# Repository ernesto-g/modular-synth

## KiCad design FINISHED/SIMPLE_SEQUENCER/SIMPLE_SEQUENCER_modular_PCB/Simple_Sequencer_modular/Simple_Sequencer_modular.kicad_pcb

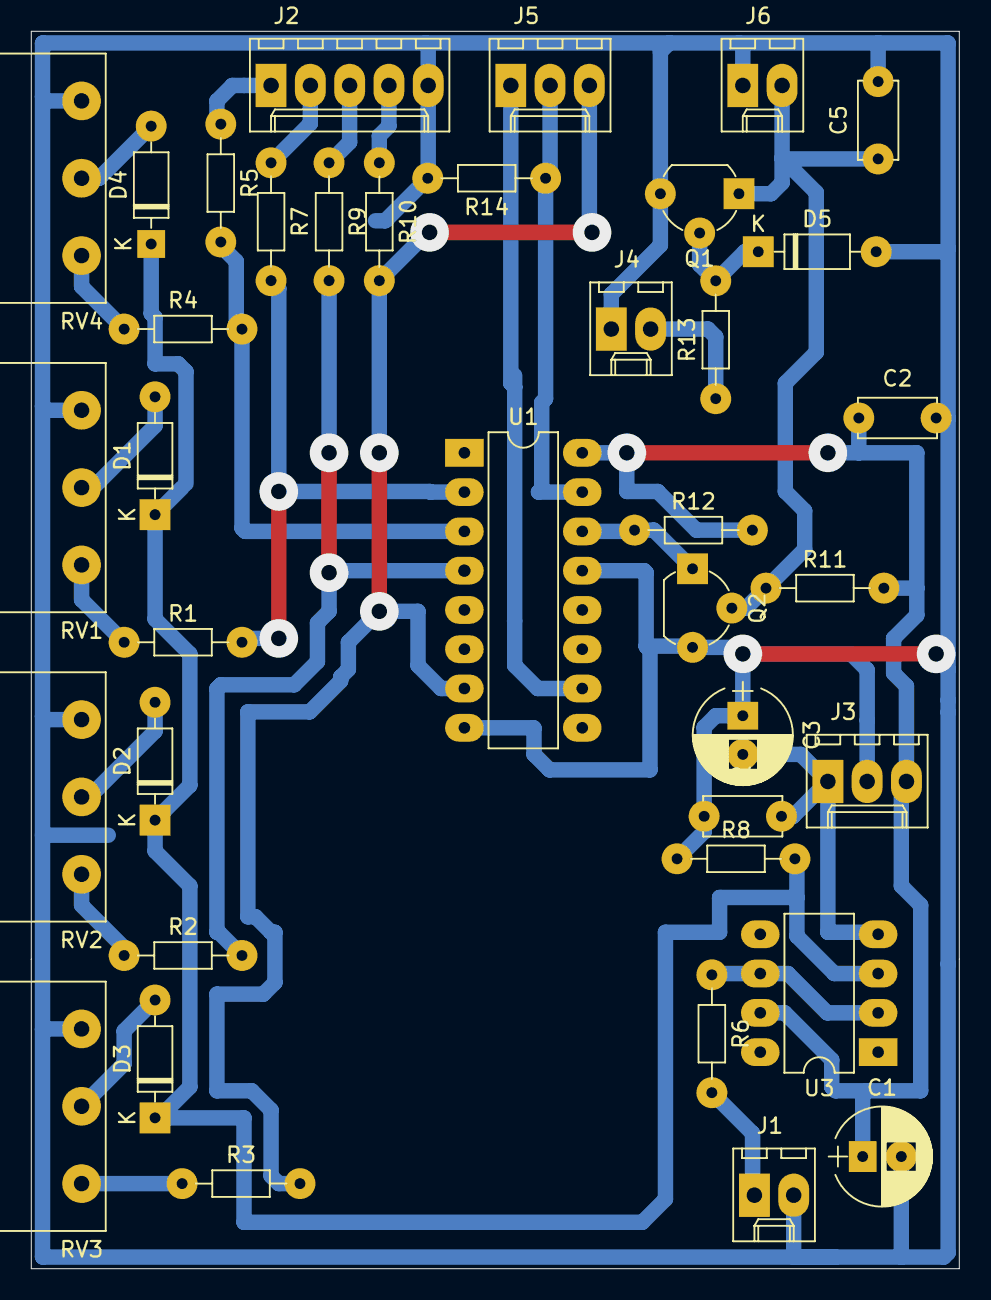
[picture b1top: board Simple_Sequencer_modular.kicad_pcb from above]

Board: 2 copper layers, 60.0 x 80.0 mm, 38 parts (0 on the bottom side), 28 nets.

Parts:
C1, C3: 100uFx25V; CP_Radial_D6.3mm_P2.50mm
C2, C4, C5: 100nF; C_Disc_D5.0mm_W2.5mm_P5.00mm
D1, D2, D3, D4, D5: 1N4148; D_DO-35_SOD27_P7.62mm_Horizontal
J1: CV_OUT; Molex_KK-6410-02_02x2.54mm_Straight
J2: LEDS_OUT; Molex_KK-6410-05_05x2.54mm_Straight
J3: POWER; Molex_KK-6410-03_03x2.54mm_Straight
J4: CLK_IN; Molex_KK-6410-02_02x2.54mm_Straight
J5: SW_STEPS; Molex_KK-6410-03_03x2.54mm_Straight
J6: BTN_STEP; Molex_KK-6410-02_02x2.54mm_Straight
Q1, Q2: BC547; TO-92_Wide
R1, R2, R3, R4: 10k; R_Axial_DIN0204_L3.6mm_D1.6mm_P7.62mm_Horizontal
R5, R7, R9, R10: 2.2k; R_Axial_DIN0204_L3.6mm_D1.6mm_P7.62mm_Horizontal
R6: 100; R_Axial_DIN0204_L3.6mm_D1.6mm_P7.62mm_Horizontal
R8, R11, R12, R13, R14: 100k; R_Axial_DIN0204_L3.6mm_D1.6mm_P7.62mm_Horizontal
RV1, RV2, RV3, RV4: 10K B; Potentiometer_Piher_PC-16_Single_Vertical
U1: 4017; DIP-16_W7.62mm_LongPads
U3: LM741; DIP-8_W7.62mm_LongPads

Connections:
+12V: C1.1, C2.1, J3.3, R11.2, R12.2, U1.16, U3.7
-12V: C3.2, C4.2, J3.1, U3.4
CLK: Q2.1, R12.1, U1.14
GND: C1.2, C2.2, C3.1, C4.1, C5.2, D5.2, J1.2, J2.5, J3.2, J4.1, J6.1, Q1.3, Q2.3, R8.1, R14.2, RV1.1, RV2.1, RV3.1, RV4.1, U1.8, U1.13
unnamed: C5.1, J6.2, Q1.1, Q2.2, R11.1
unnamed: D1.2, RV1.2
unnamed: D2.2, RV2.2
unnamed: D3.2, RV3.2
unnamed: D4.2, RV4.2
unnamed: D5.1, Q1.2, R13.2
unnamed: J1.1, R6.2
unnamed: J2.1, R5.1
unnamed: J2.2, R7.1
unnamed: J2.3, R9.1
unnamed: J2.4, R10.1
unnamed: J4.2, R13.1
unnamed: R1.1, RV1.3
unnamed: R2.1, RV2.3
unnamed: R3.1, RV3.3
unnamed: R4.1, RV4.3
unnamed: R6.1, U3.2, U3.6
Q0: R4.2, R5.2, U1.3
Q0_CV: D1.1, D2.1, D3.1, D4.1, R8.2, U3.3
Q1: R1.2, R7.2, U1.2
Q2: R2.2, R9.2, U1.4
Q3: J5.3, R3.2, R10.2, U1.7
Q4: J5.1, U1.10
RST: J5.2, R14.1, U1.15

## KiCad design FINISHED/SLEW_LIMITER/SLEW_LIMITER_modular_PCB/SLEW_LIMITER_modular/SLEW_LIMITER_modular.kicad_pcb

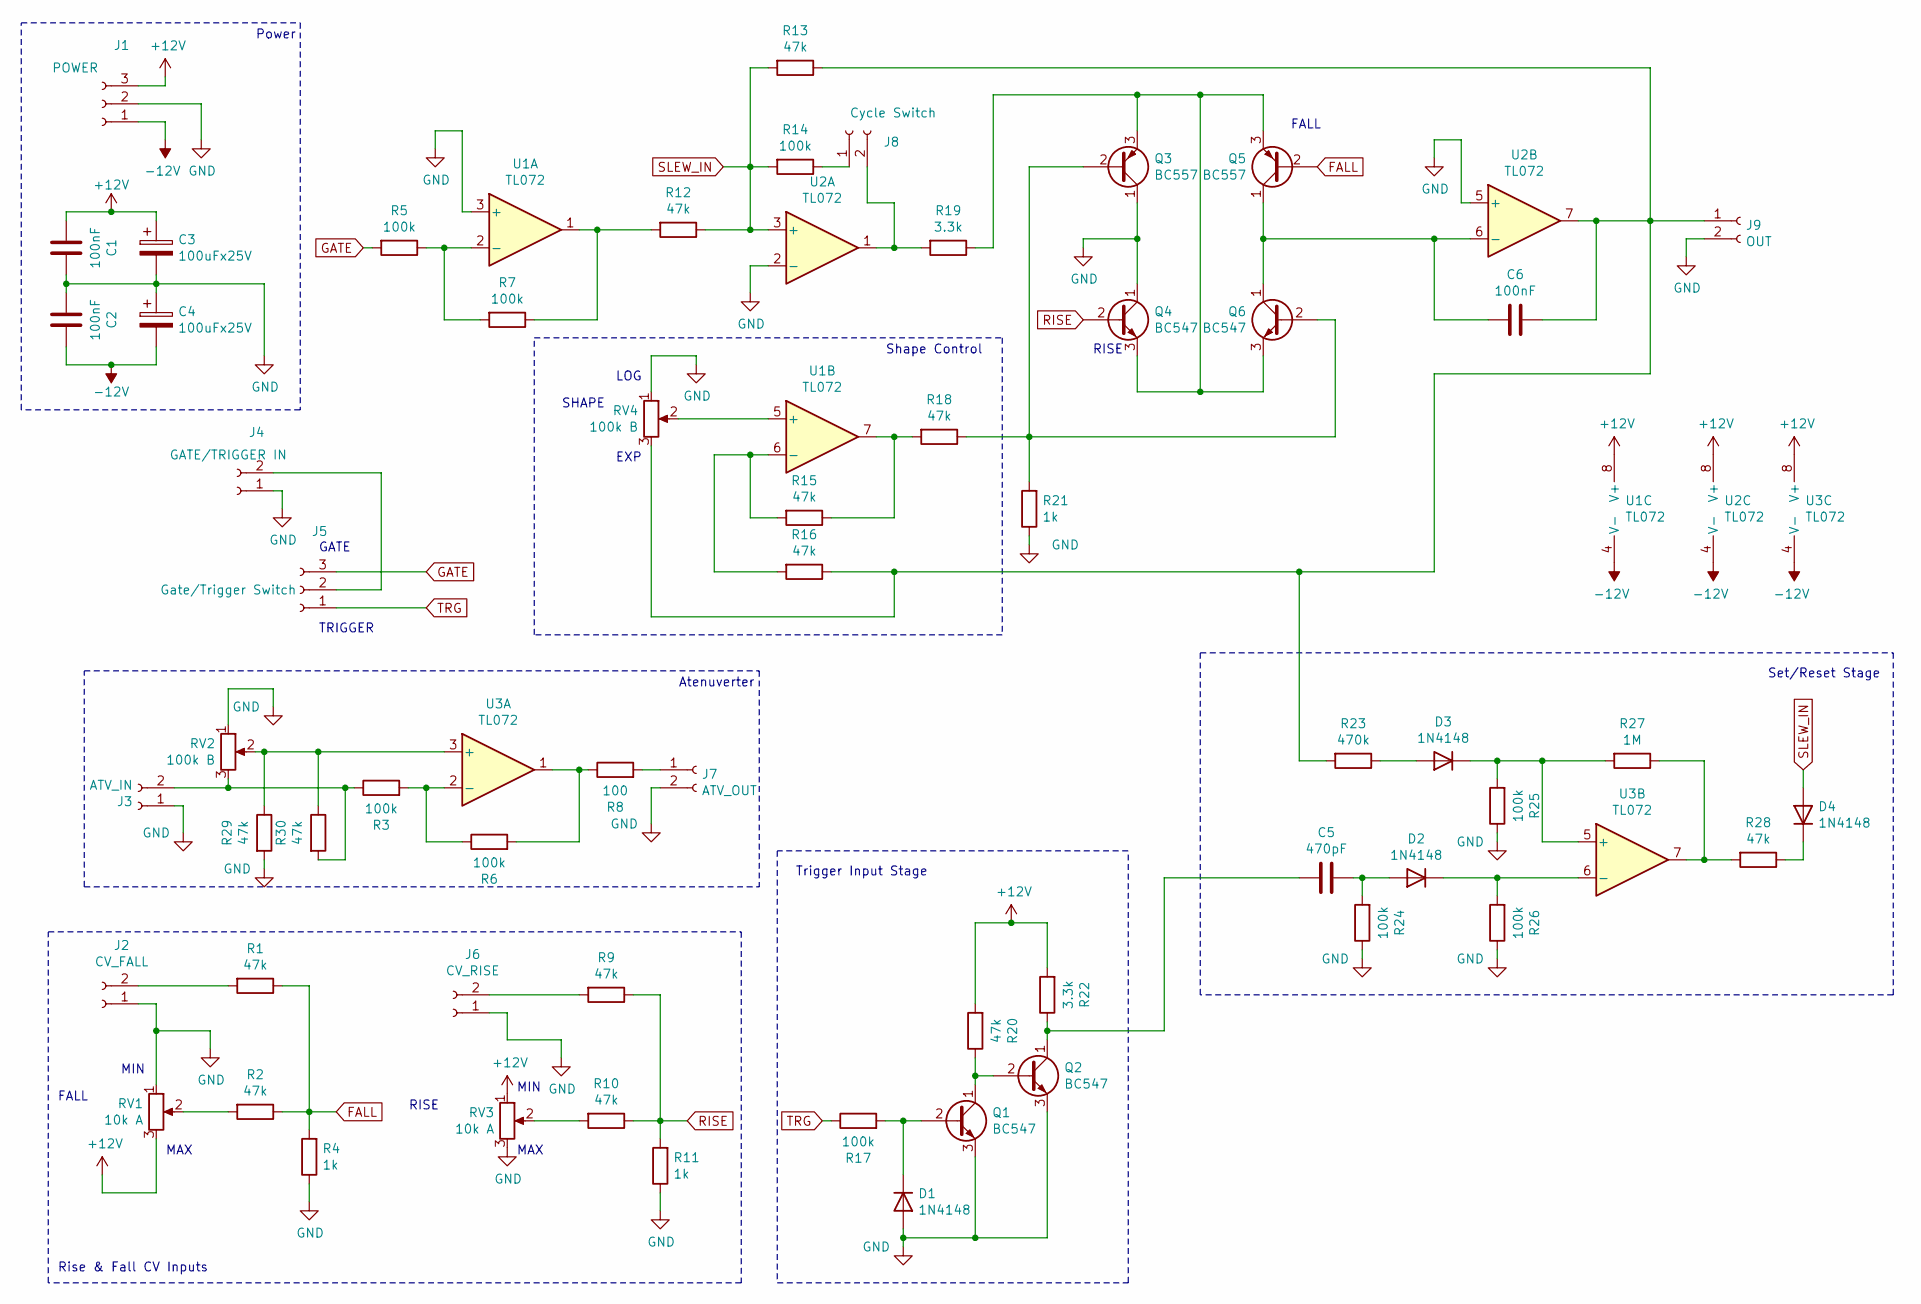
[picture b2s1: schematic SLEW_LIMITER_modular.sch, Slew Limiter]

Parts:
C1, C2, C6: 100nF; C_Disc_D5.0mm_W2.5mm_P5.00mm
C3, C4: 100uFx25V; CP_Radial_D6.3mm_P2.50mm
C5: 470pF; C_Disc_D5.0mm_W2.5mm_P5.00mm
D1, D2, D3, D4: 1N4148; D_DO-35_SOD27_P7.62mm_Horizontal
J1: POWER; Molex_KK-6410-03_03x2.54mm_Straight
J2: CV_FALL; Molex_KK-6410-02_02x2.54mm_Straight
J3: ATV_IN; Molex_KK-6410-02_02x2.54mm_Straight
J4: GATE/TRIGGER IN; Molex_KK-6410-02_02x2.54mm_Straight
J5: Gate/Trigger Switch; Molex_KK-6410-03_03x2.54mm_Straight
J6: CV_RISE; Molex_KK-6410-02_02x2.54mm_Straight
J7: ATV_OUT; Molex_KK-6410-02_02x2.54mm_Straight
J8: Cycle Switch; Molex_KK-6410-02_02x2.54mm_Straight
J9: OUT; Molex_KK-6410-02_02x2.54mm_Straight
Q1, Q2, Q4, Q6: BC547; TO-92L_HandSolder
Q3, Q5: BC557; TO-92L_HandSolder
R1, R2, R9, R10, R12, R13, R15, R16, R18, R20, R28, R29, R30: 47k; R_Axial_DIN0204_L3.6mm_D1.6mm_P7.62mm_Horizontal
R3, R5, R6, R7, R14, R17, R24, R25, R26: 100k; R_Axial_DIN0204_L3.6mm_D1.6mm_P7.62mm_Horizontal
R4, R11, R21: 1k; R_Axial_DIN0204_L3.6mm_D1.6mm_P7.62mm_Horizontal
R8: 100; R_Axial_DIN0204_L3.6mm_D1.6mm_P7.62mm_Horizontal
R19, R22: 3.3k; R_Axial_DIN0204_L3.6mm_D1.6mm_P7.62mm_Horizontal
R23: 470k; R_Axial_DIN0204_L3.6mm_D1.6mm_P7.62mm_Horizontal
R27: 1M; R_Axial_DIN0204_L3.6mm_D1.6mm_P7.62mm_Horizontal
RV1, RV3: 10k A; Potentiometer_Piher_PC-16_Single_Vertical
RV2, RV4: 100k B; Potentiometer_Piher_PC-16_Single_Vertical
U1, U2, U3: TL072; DIP-8_W7.62mm_Socket_LongPads

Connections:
+12V: C1.2, C3.1, J1.3, R20.2, R22.2, RV1.3, RV3.1, U1.8 (V+), U2.8 (V+), U3.8 (V+)
-12V: C2.1, C4.2, J1.1, U1.4 (V-), U2.4 (V-), U3.4 (V-)
FALL: Q5.2 (B), R1.1, R2.1, R4.2
GATE: J5.3, R5.2
GND: C1.1, C2.2, C3.2, C4.1, D1.2 (A), J1.2, J2.1, J3.1, J4.1, J6.1, J7.2, J9.2, Q1.3 (E), Q2.3 (E), Q3.1 (C), Q4.1 (C), R4.1, R11.1, R21.1, R24.1, R25.1, R26.1, R29.2, RV1.1, RV2.1, RV3.3, RV4.1, U1.3 (+), U2.2 (-), U2.5 (+)
unnamed: C5.1, D2.2 (A), R24.2
unnamed: C5.2, Q2.1 (C), R22.1
unnamed: C6.1, J9.1, R13.1, R16.1, R23.2, RV4.3, U2.7
unnamed: C6.2, Q5.1 (C), Q6.1 (C), U2.6 (-)
unnamed: D1.1 (K), Q1.2 (B), R17.2
unnamed: D2.1 (K), R26.2, U3.6 (-)
unnamed: D3.1 (K), R25.2, R27.2, U3.5 (+)
unnamed: D3.2 (A), R23.1
unnamed: D4.1 (K), R28.1
unnamed: J2.2, R1.2
unnamed: J3.2, R3.1, R30.2, RV2.3
unnamed: J4.2, J5.2
unnamed: J6.2, R9.2
unnamed: J7.1, R8.2
unnamed: J8.1, R14.1
unnamed: J8.2, R19.2, U2.1
unnamed: Q1.1 (C), Q2.2 (B), R20.1
unnamed: Q3.2 (B), Q6.2 (B), R18.1, R21.2
unnamed: Q3.3 (E), Q4.3 (E), Q5.3 (E), Q6.3 (E), R19.1
unnamed: R2.2, RV1.2
unnamed: R3.2, R6.1, U3.2 (-)
unnamed: R5.1, R7.2, U1.2 (-)
unnamed: R6.2, R8.1, U3.1
unnamed: R10.2, RV3.2
unnamed: R7.1, R12.2, U1.1
unnamed: R15.1, R18.2, U1.7
unnamed: R15.2, R16.2, U1.6 (-)
unnamed: R27.1, R28.2, U3.7
unnamed: R29.1, R30.1, RV2.2, U3.3 (+)
unnamed: RV4.2, U1.5 (+)
RISE: Q4.2 (B), R9.1, R10.1, R11.2
SLEW_IN: D4.2 (A), R12.1, R13.2, R14.2, U2.3 (+)
TRG: J5.1, R17.1

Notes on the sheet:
RISE
FALL
Shape Control
SHAPE
LOG
EXP
MAX
MIN
TRIGGER
GATE
Atenuverter
Trigger Input Stage
Set/Reset Stage
Rise & Fall CV Inputs
Power

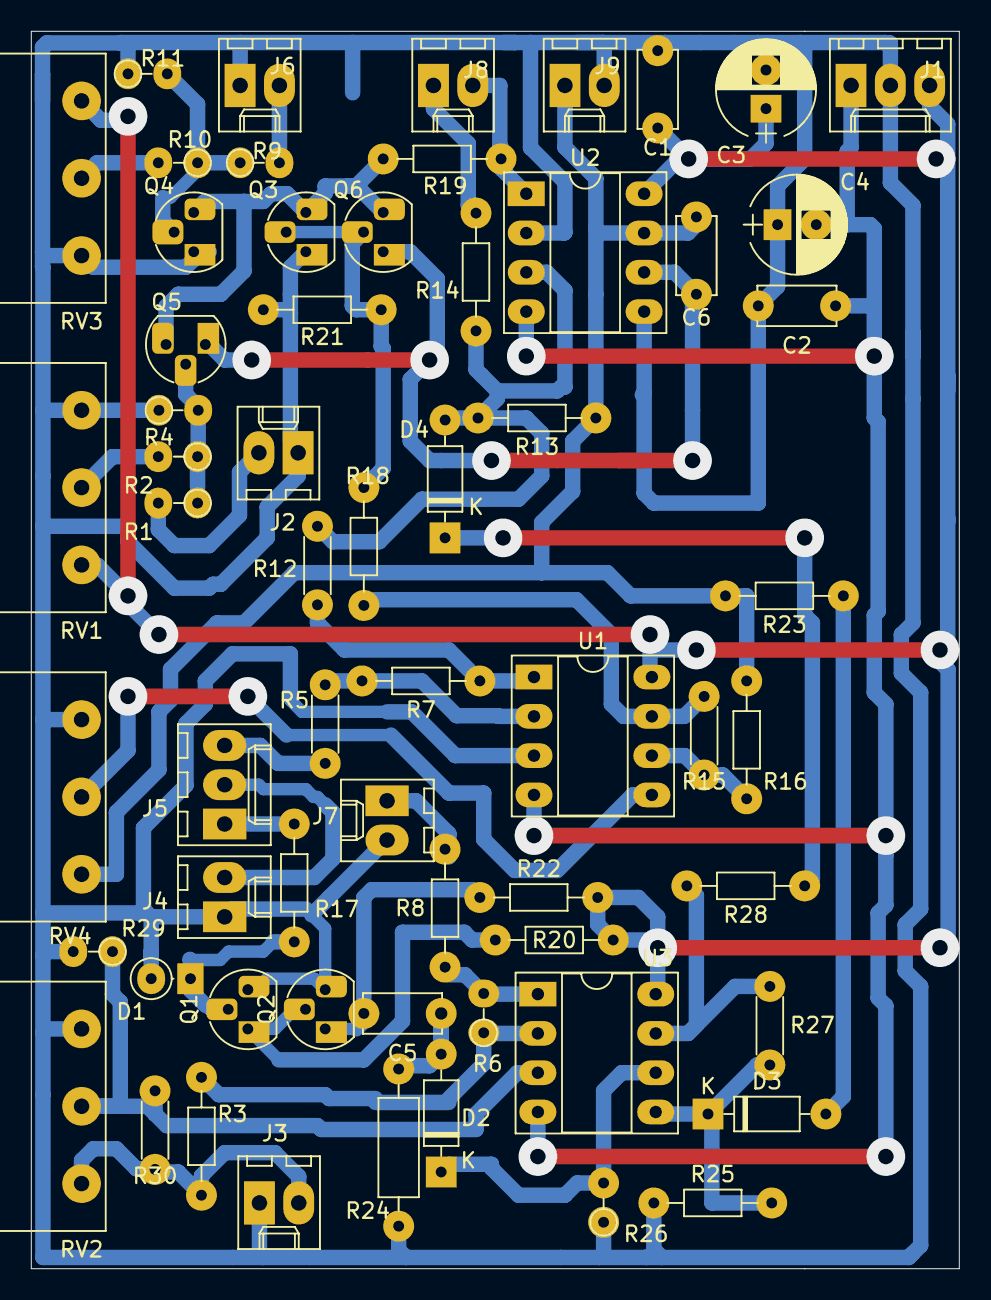
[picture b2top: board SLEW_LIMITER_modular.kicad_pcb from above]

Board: 2 copper layers, 60.0 x 80.0 mm, 62 parts (0 on the bottom side), 38 nets.

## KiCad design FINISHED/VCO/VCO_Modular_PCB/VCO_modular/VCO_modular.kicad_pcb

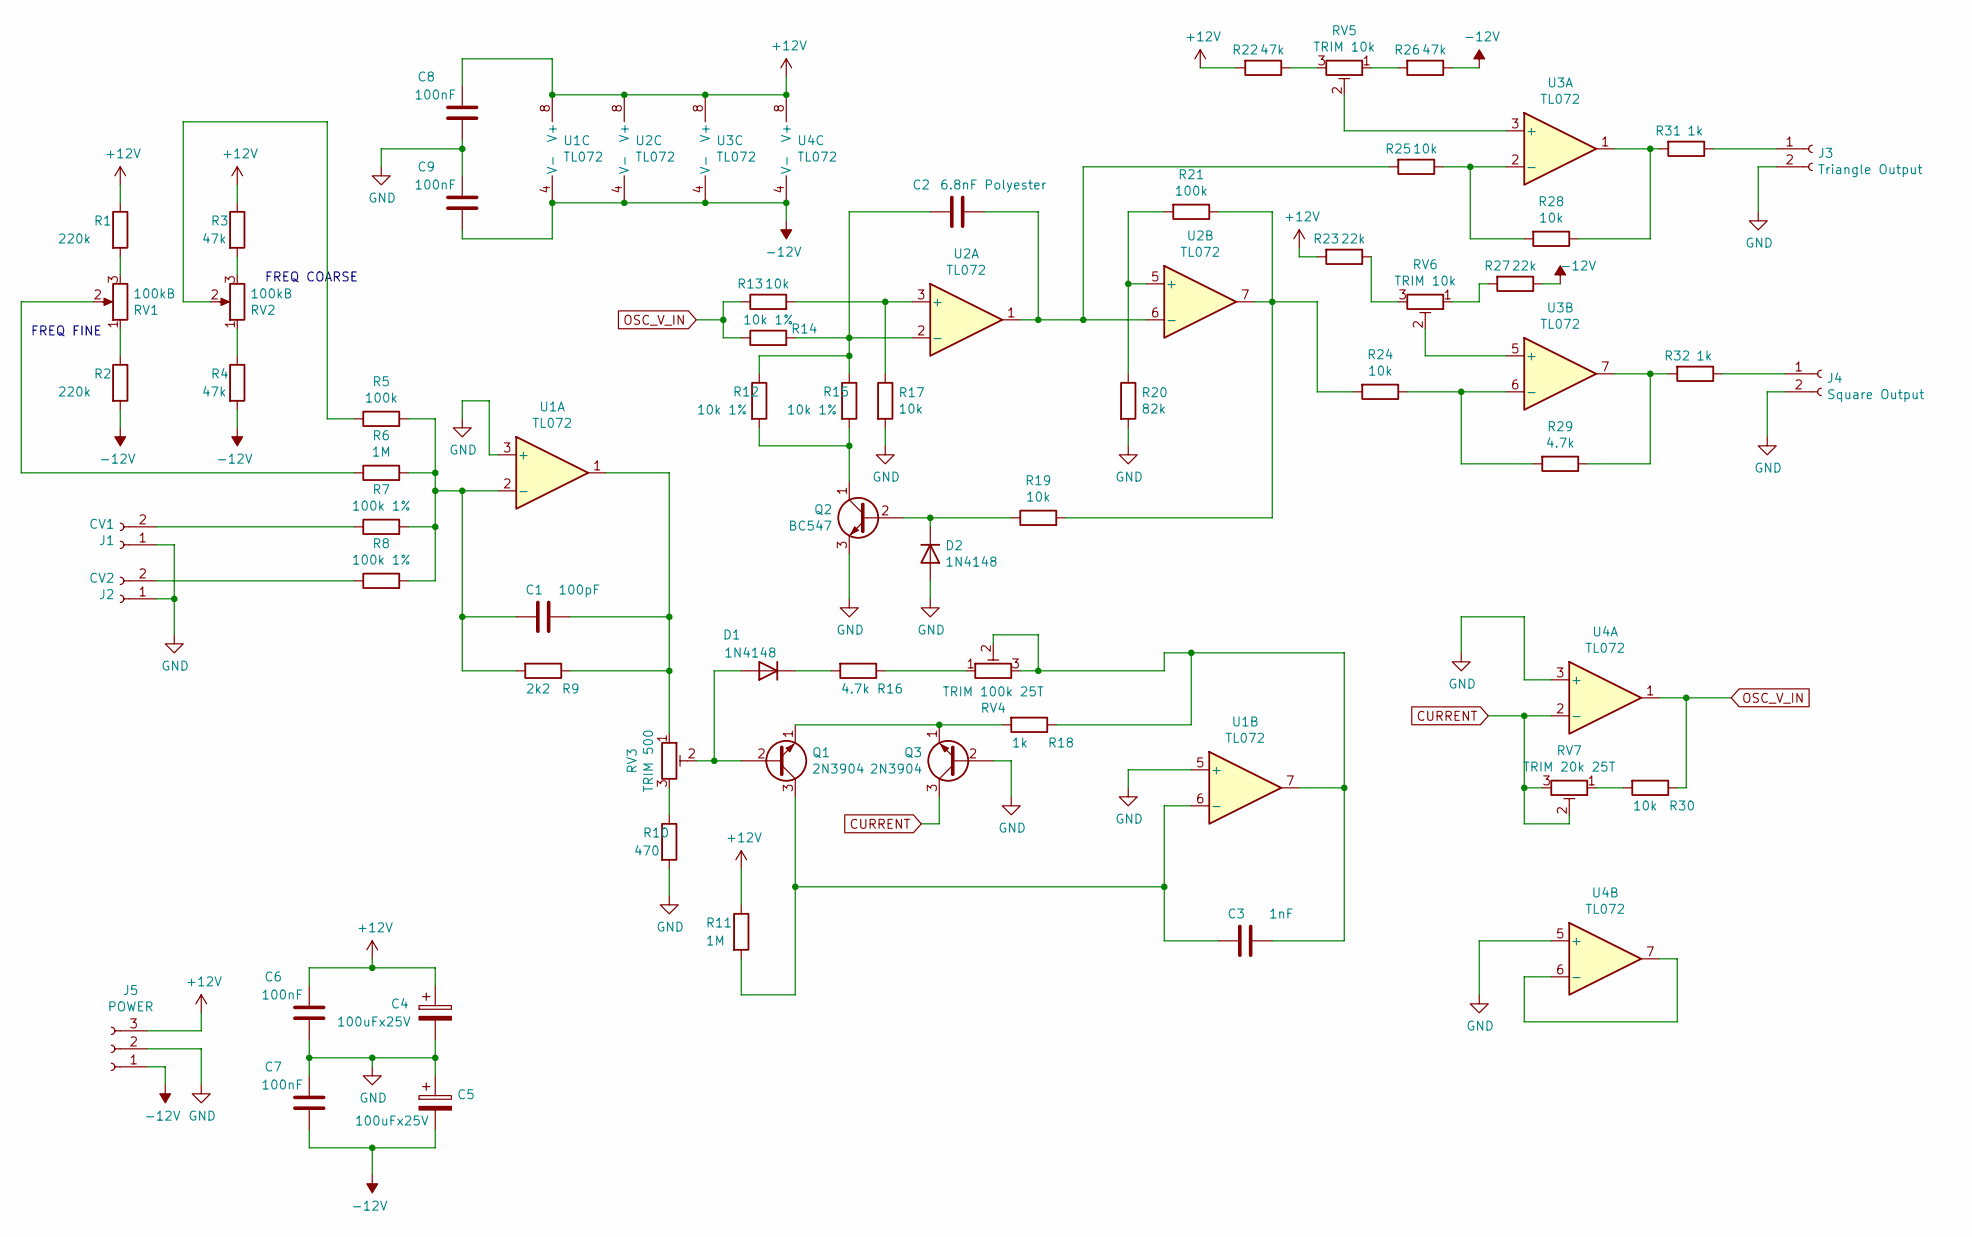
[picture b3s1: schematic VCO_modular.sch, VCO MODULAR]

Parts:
C1: 100pF; C_Disc_D5.0mm_W2.5mm_P5.00mm
C2: 6.8nF Polyester; C_Disc_D5.0mm_W2.5mm_P5.00mm
C3: 1nF; C_Disc_D5.0mm_W2.5mm_P5.00mm
C4, C5: 100uFx25V; CP_Radial_D8.0mm_P3.50mm
C6, C7, C8, C9: 100nF; C_Disc_D7.5mm_W2.5mm_P5.00mm
D1, D2: 1N4148; D_DO-41_SOD81_P7.62mm_Horizontal
J1: CV1; Molex_KK-6410-02_02x2.54mm_Straight
J2: CV2; Molex_KK-6410-02_02x2.54mm_Straight
J3: Triangle Output; Molex_KK-6410-02_02x2.54mm_Straight
J4: Square Output; Molex_KK-6410-02_02x2.54mm_Straight
J5: POWER; Molex_KK-6410-03_03x2.54mm_Straight
Q1, Q3: 2N3904; TO-92L_HandSolder
Q2: BC547; TO-92L_HandSolder
R1, R2: 220k; R_Axial_DIN0207_L6.3mm_D2.5mm_P7.62mm_Horizontal
R3, R4, R22, R26: 47k; R_Axial_DIN0207_L6.3mm_D2.5mm_P7.62mm_Horizontal
R5, R21: 100k; R_Axial_DIN0207_L6.3mm_D2.5mm_P7.62mm_Horizontal
R6, R11: 1M; R_Axial_DIN0207_L6.3mm_D2.5mm_P7.62mm_Horizontal
R7, R8: 100k 1%; R_Axial_DIN0207_L6.3mm_D2.5mm_P7.62mm_Horizontal
R9: 2k2; R_Axial_DIN0207_L6.3mm_D2.5mm_P7.62mm_Horizontal
R10: 470; R_Axial_DIN0207_L6.3mm_D2.5mm_P7.62mm_Horizontal
R12, R14, R15: 10k 1%; R_Axial_DIN0207_L6.3mm_D2.5mm_P7.62mm_Horizontal
R13, R17, R19, R24, R25, R28, R30: 10k; R_Axial_DIN0207_L6.3mm_D2.5mm_P7.62mm_Horizontal
R16, R29: 4.7k; R_Axial_DIN0207_L6.3mm_D2.5mm_P7.62mm_Horizontal
R18, R31, R32: 1k; R_Axial_DIN0207_L6.3mm_D2.5mm_P7.62mm_Horizontal
R20: 82k; R_Axial_DIN0207_L6.3mm_D2.5mm_P7.62mm_Horizontal
R23, R27: 22k; R_Axial_DIN0207_L6.3mm_D2.5mm_P7.62mm_Horizontal
RV1, RV2: 100kB; Potentiometer_Alps_RK163_Single_Vertical
RV3: TRIM 500; Potentiometer_Trimmer_Bourns_3266Y
RV4: TRIM 100k 25T; Potentiometer_Trimmer_Bourns_3296W
RV5: TRIM 10k; Potentiometer_Trimmer_ACP_CA6v_Horizontal
RV6: TRIM 10k; Potentiometer_Trimmer_Bourns_3296Y
RV7: TRIM 20k 25T; Potentiometer_Trimmer_Bourns_3296W
U1, U2, U3, U4: TL072; DIP-8_W7.62mm_LongPads

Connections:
+12V: C4.1, C6.2, C8.2, J5.3, R1.1, R3.1, R11.1, R22.2, R23.2, U1.8 (V+), U2.8 (V+), U3.8 (V+), U4.8 (V+)
-12V: C5.2, C7.1, C9.1, J5.1, R2.2, R4.2, R26.1, R27.1, U1.4 (V-), U2.4 (V-), U3.4 (V-), U4.4 (V-)
CURRENT: Q3.3 (C), RV7.2, RV7.3, U4.2 (-)
GND: C4.2, C5.1, C6.1, C7.2, C8.1, C9.2, D2.2 (A), J1.1, J2.1, J3.2, J4.2, J5.2, Q2.3 (E), Q3.2 (B), R10.2, R17.2, R20.2, U1.3 (+), U1.5 (+), U4.3 (+), U4.5 (+)
unnamed: C1.1, R9.1, RV3.1, U1.1
unnamed: C1.2, R5.2, R6.2, R7.2, R8.2, R9.2, U1.2 (-)
unnamed: C2.1, R25.2, U2.1, U2.6 (-)
unnamed: C2.2, R12.1, R14.2, R15.1, U2.2 (-)
unnamed: C3.1, R18.1, RV4.2, RV4.3, U1.7
unnamed: C3.2, Q1.3 (C), R11.2, U1.6 (-)
unnamed: D1.1 (K), R16.2
unnamed: D1.2 (A), Q1.2 (B), RV3.2
unnamed: D2.1 (K), Q2.2 (B), R19.1
unnamed: J1.2, R7.1
unnamed: J2.2, R8.1
unnamed: J3.1, R31.1
unnamed: J4.1, R32.1
unnamed: Q1.1 (E), Q3.1 (E), R18.2
unnamed: Q2.1 (C), R12.2, R15.2
unnamed: R1.2, RV1.3
unnamed: R2.1, RV1.1
unnamed: R3.2, RV2.3
unnamed: R4.1, RV2.1
unnamed: R5.1, RV2.2
unnamed: R6.1, RV1.2
unnamed: R10.1, RV3.3
unnamed: R13.2, R17.1, U2.3 (+)
unnamed: R16.1, RV4.1
unnamed: R19.2, R21.1, R24.2, U2.7
unnamed: R20.1, R21.2, U2.5 (+)
unnamed: R22.1, RV5.3
unnamed: R23.1, RV6.3
unnamed: R24.1, R29.2, U3.6 (-)
unnamed: R25.1, R28.2, U3.2 (-)
unnamed: R26.2, RV5.1
unnamed: R27.2, RV6.1
unnamed: R28.1, R31.2, U3.1
unnamed: R29.1, R32.2, U3.7
unnamed: R30.2, RV7.1
unnamed: RV5.2, U3.3 (+)
unnamed: RV6.2, U3.5 (+)
unnamed: U4.6 (-), U4.7
OSC_V_IN: R13.1, R14.1, R30.1, U4.1

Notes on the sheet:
FREQ FINE
FREQ COARSE

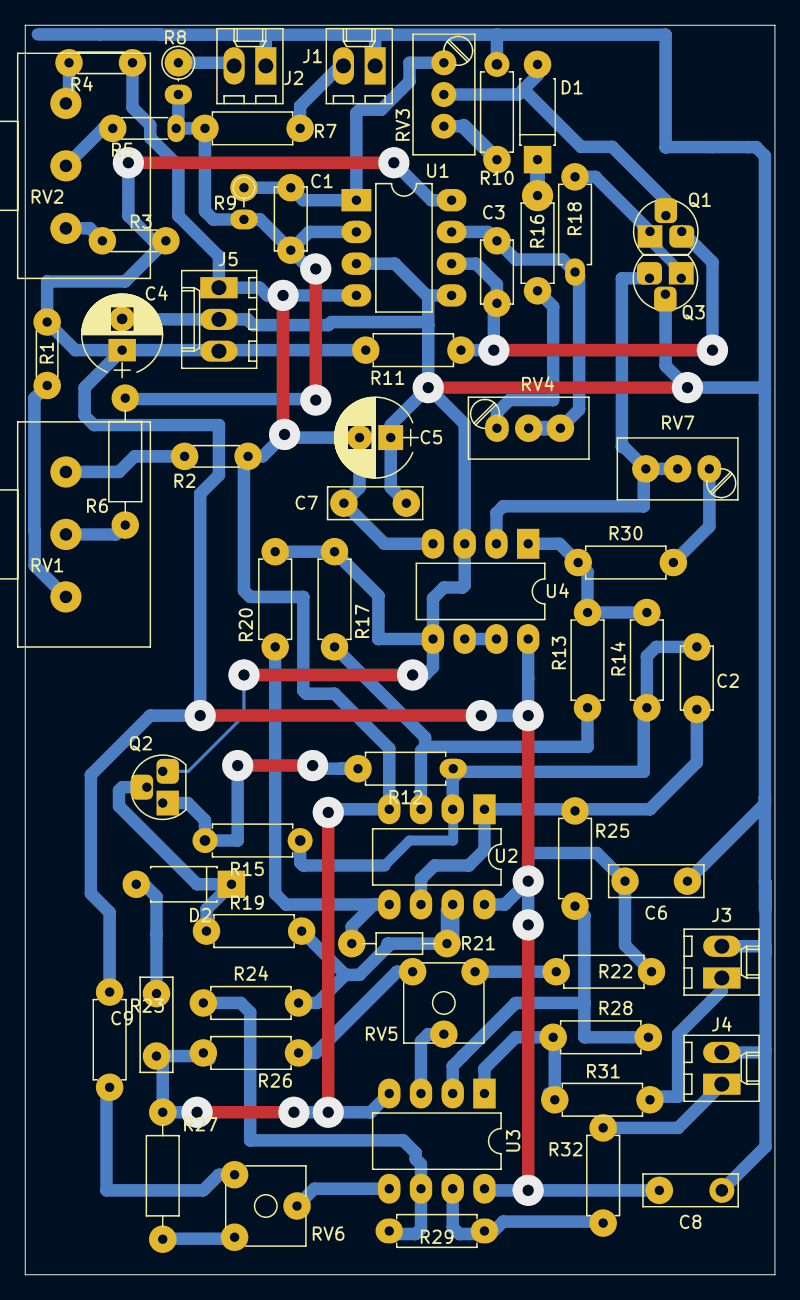
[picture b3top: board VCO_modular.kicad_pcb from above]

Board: 2 copper layers, 60.0 x 100.0 mm, 62 parts (0 on the bottom side), 43 nets.

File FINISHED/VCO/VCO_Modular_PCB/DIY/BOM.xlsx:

|  | C1 | 100pF | Capacitors_ThroughHole:C_Disc_D5.0mm_W2.5mm_P5.00mm | 1
 |  | C2 | 6.8nF Polyester | Capacitors_ThroughHole:C_Disc_D5.0mm_W2.5mm_P5.00mm | 1
 |  | C3 | 1nF | Capacitors_ThroughHole:C_Disc_D5.0mm_W2.5mm_P5.00mm | 1
 |  | > C4, C5 | 100uFx25V | Capacitors_ThroughHole:CP_Radial_D8.0mm_P3.50mm | 2
 |  | > C6-C9 | 100nF | Capacitors_ThroughHole:C_Disc_D7.5mm_W2.5mm_P5.00mm | 4
 |  | > D1, D2 | 1N4148 | Diodes_ThroughHole:D_DO-41_SOD81_P7.62mm_Horizontal | 2
 |  | J1 | CV1 | Connectors_Molex:Molex_KK-6410-02_02x2.54mm_Straight | 1
 |  | J2 | CV2 | Connectors_Molex:Molex_KK-6410-02_02x2.54mm_Straight | 1
 |  | J3 | Triangle Output | Connectors_Molex:Molex_KK-6410-02_02x2.54mm_Straight | 1
 |  | J4 | Square Output | Connectors_Molex:Molex_KK-6410-02_02x2.54mm_Straight | 1
 |  | J5 | POWER | Connectors_Molex:Molex_KK-6410-03_03x2.54mm_Straight | 1
 |  | > Q1, Q3 | 2N3904 | Package_TO_SOT_THT:TO-92L_HandSolder | 2
 |  | Q2 | BC547 | Package_TO_SOT_THT:TO-92L_HandSolder | 1
 |  | > R1, R2 | 220k | Resistors_ThroughHole:R_Axial_DIN0207_L6.3mm_D2.5mm_P7.62mm_Horizontal | 2
 |  | > R6, R11 | 1M | Resistors_ThroughHole:R_Axial_DIN0207_L6.3mm_D2.5mm_P7.62mm_Horizontal | 2
 |  | > R7, R8 | 100k 1% | Resistors_ThroughHole:R_Axial_DIN0207_L6.3mm_D2.5mm_P7.62mm_Horizontal | 2
 |  | R9 | 2k2 | Resistors_ThroughHole:R_Axial_DIN0207_L6.3mm_D2.5mm_P7.62mm_Horizontal | 1
 |  | R10 | 470 | Resistors_ThroughHole:R_Axial_DIN0207_L6.3mm_D2.5mm_P7.62mm_Horizontal | 1
 |  | > R13, R17, R19, R24, R25, R28, R30 | 10k | Resistors_ThroughHole:R_Axial_DIN0207_L6.3mm_D2.5mm_P7.62mm_Horizontal | 7
 |  | > R12, R14, R15 | 10k 1% | Resistors_ThroughHole:R_Axial_DIN0207_L6.3mm_D2.5mm_P7.62mm_Horizontal | 3
 |  | R20 | 82k | Resistors_ThroughHole:R_Axial_DIN0207_L6.3mm_D2.5mm_P7.62mm_Horizontal | 1
 |  | > R5, R21 | 100k | Resistors_ThroughHole:R_Axial_DIN0207_L6.3mm_D2.5mm_P7.62mm_Horizontal | 2
 |  | > R23, R27 | 22k | Resistors_ThroughHole:R_Axial_DIN0207_L6.3mm_D2.5mm_P7.62mm_Horizontal | 2
 |  | > R3, R4, R22, R26 | 47k | Resistors_ThroughHole:R_Axial_DIN0207_L6.3mm_D2.5mm_P7.62mm_Horizontal | 4
 |  | > R16, R29 | 4.7k | Resistors_ThroughHole:R_Axial_DIN0207_L6.3mm_D2.5mm_P7.62mm_Horizontal | 2
 |  | > R18, R31, R32 | 1k | Resistors_ThroughHole:R_Axial_DIN0207_L6.3mm_D2.5mm_P7.62mm_Horizontal | 3
 |  | > RV1, RV2 | 100kB | Potentiometers:Potentiometer_Alps_RK163_Single_Vertical | 2
 |  | RV3 | TRIM 500 | Potentiometers:Potentiometer_Trimmer_Bourns_3266Y | 1
 |  | RV4 | TRIM 100k 25T | Potentiometers:Potentiometer_Trimmer_Bourns_3296W | 1
 |  | RV5 | TRIM 10k | Potentiometers:Potentiometer_Trimmer_ACP_CA6v_Horizontal | 1
 |  | RV6 | TRIM 10k | Potentiometers:Potentiometer_Trimmer_Bourns_3296Y | 1
 |  | RV7 | TRIM 20k 25T | Potentiometers:Potentiometer_Trimmer_Bourns_3296W | 1
 |  | > U1-U4 | TL072 | Housings_DIP:DIP-8_W7.62mm_LongPads | 4
 |  |  | Banana jack |  | 4
